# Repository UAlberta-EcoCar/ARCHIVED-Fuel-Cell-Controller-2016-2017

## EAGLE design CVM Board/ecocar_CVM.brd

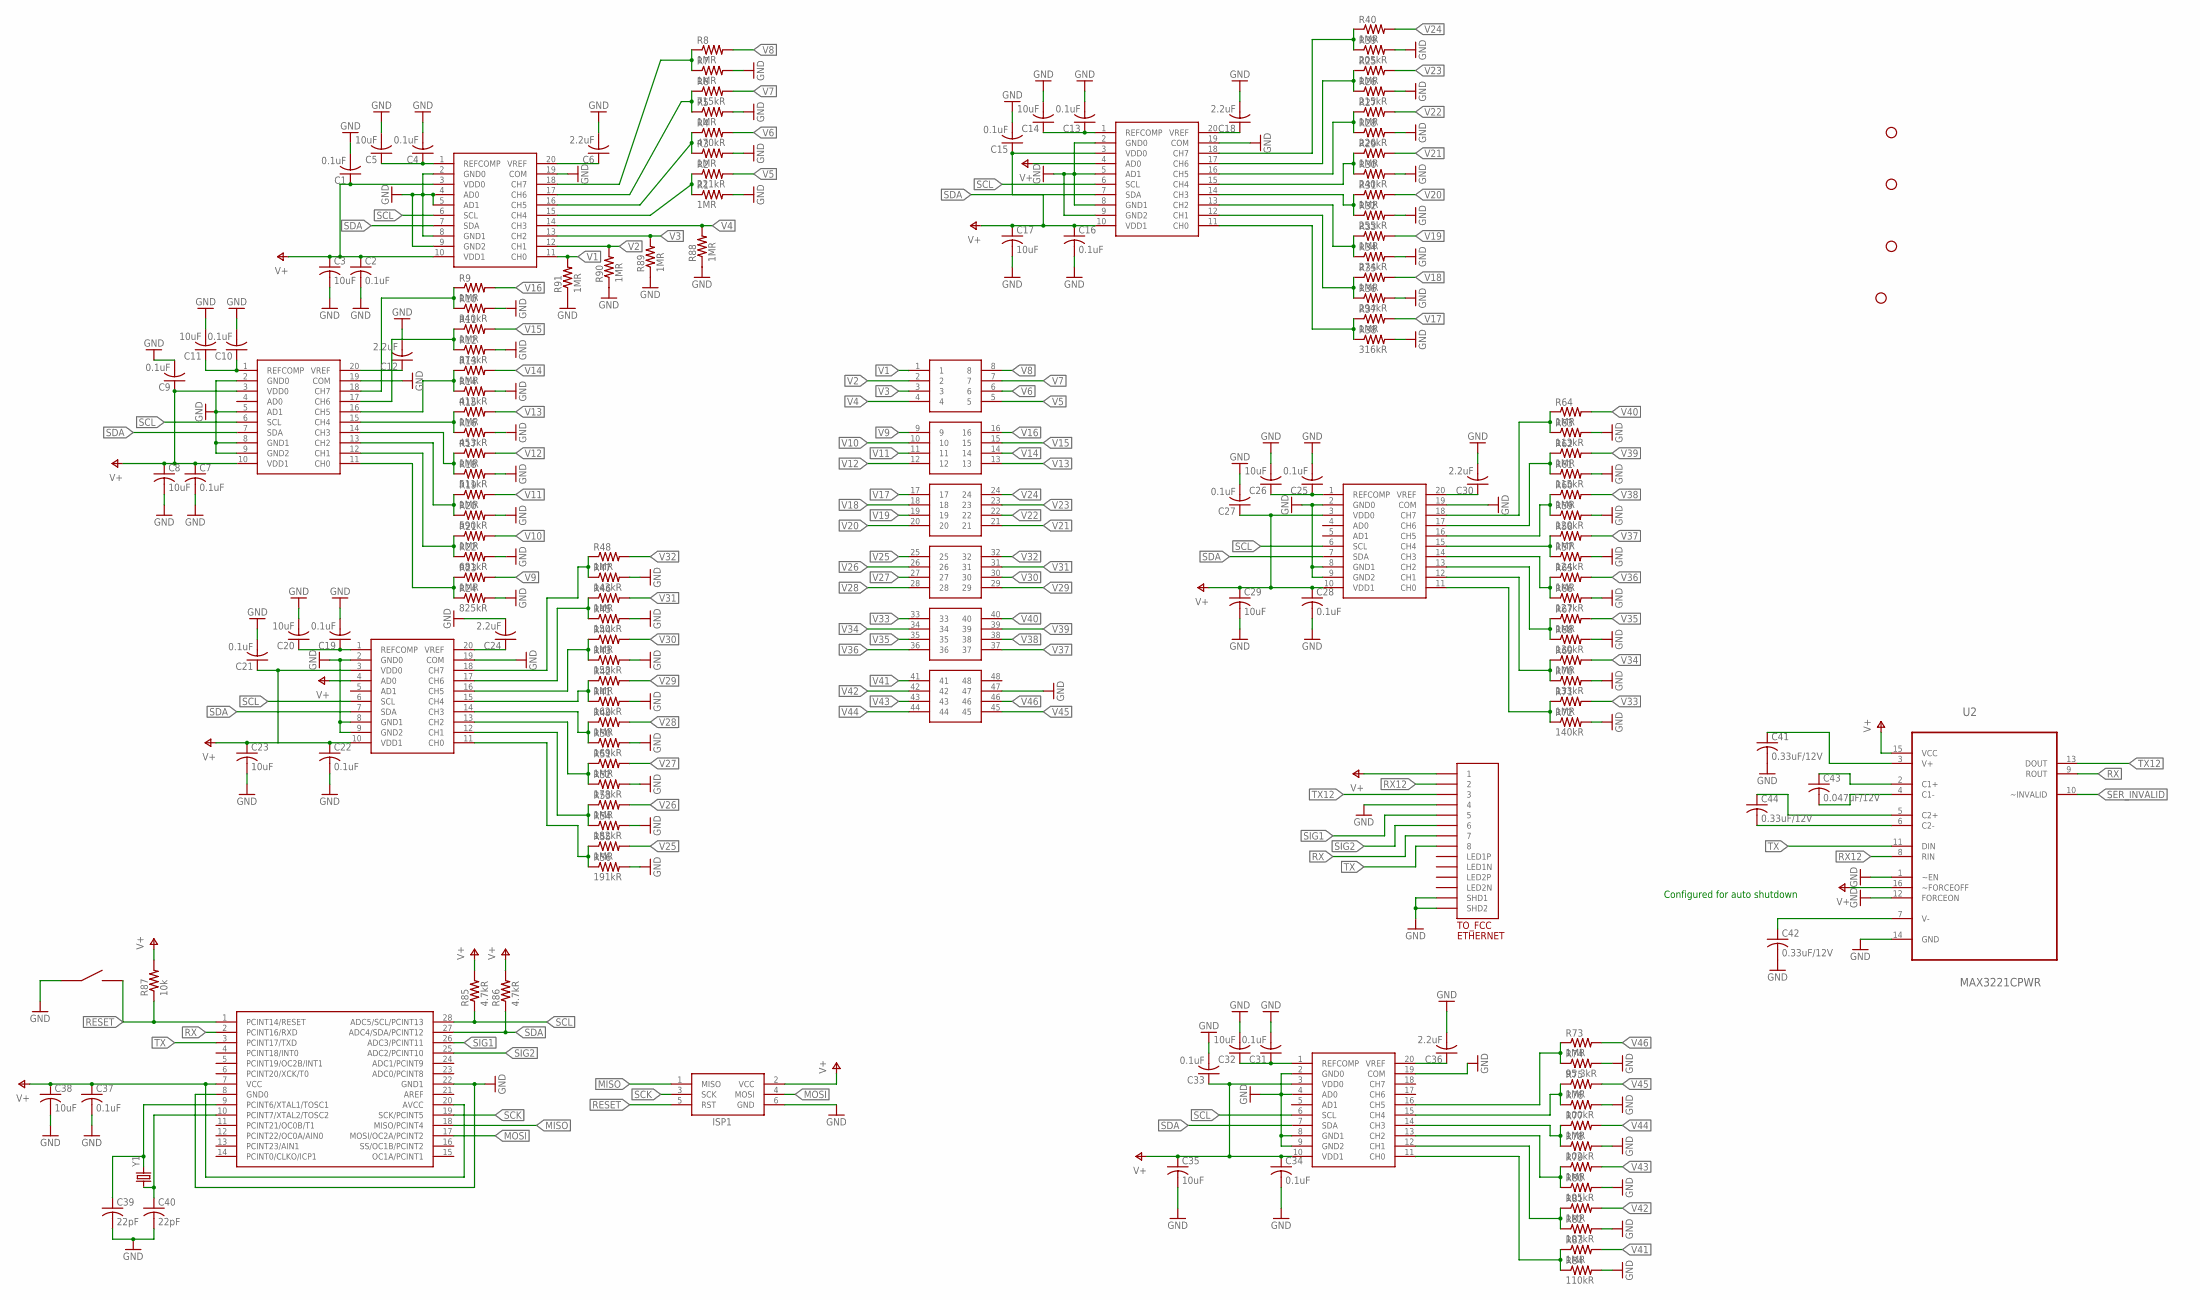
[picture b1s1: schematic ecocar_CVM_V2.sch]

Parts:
0001000, 0001001, 0001010, 0001011, 0011000, 0011001: LTC2309; TSSOP20
C1, C2, C4, C7, C9, C10, C13, C15, C16, C19, C21, C22, C25, C27, C28, C31, C33, C34, C37: 0.1uF; C0805
C3, C5, C8, C11, C14, C17, C20, C23, C26, C29, C32, C35, C38: 10uF; C0805
C6, C12, C18, C24, C30, C36: 2.2uF; C0805
C39, C40: 22pF; C0805
C41, C42, C44: 0.33uF/12V; C0805
C43: 0.047uF/12V; C0805
ISP1: AVRISP-BOX
R1, R3, R5, R7, R8, R9, R11, R13, R15, R17, R19, R21, R23, R25, R27, R29, R31, R33, R35, R37, R40, R42, R44, R46, R48, R49, R51, R53, R55, R58, R60, R62, R64, R65, R67, R69, R71, R73, R75, R77, R79, R81, R83, R88, R89, R90, R91: 1MR; R0805
R2: 221kR; R0805
R4: 470kR; R0805
R6: 715kR; R0805
R10: 340kR; R0805
R12: 374kR; R0805
R14: 412kR; R0805
R16: 453kR; R0805
R18: 511kR; R0805
R20: 590kR; R0805
R22: 681kR; R0805
R24: 825kR; R0805
R26: 215kR; R0805
R28: 226kR; R0805
R30: 240kR; R0805
R32: 255kR; R0805
R34: 274kR; R0805
R36: 294kR; R0805
R38: 316kR; R0805
R39: 205kR; R0805
R41: 162kR; R0805
R43: 158kR; R0805
R45: 150kR; R0805
R47: 143kR; R0805
R50: 169kR; R0805
R52: 178kR; R0805
R54: 182kR; R0805
R56: 191kR; R0805
R57: 124kR; R0805
R59: 120kR; R0805
R61: 115kR; R0805
R63: 113kR; R0805
R66: 127kR; R0805
R68: 130kR; R0805
R70: 133kR; R0805
R72: 140kR; R0805
R74: 95.3kR; R0805
R76: 100kR; R0805
R78: 102kR; R0805
R80: 105kR; R0805
R82: 107kR; R0805
R84: 110kR; R0805
R85, R86: 4.7kR; R0805
R87: 10k; R0805
RESET_BTN: EG4621CT-ND
STANDOFF1, STANDOFF2, STANDOFF3, STANDOFF4: STAND-OFF
TO_FCC: ETHERNET; A122645-ND
U2: MAX3221CPWR; SOP65P640X120-16N
U$1: ATMEGA328P; DIL28-3
U$3: 6-RJ45; 48-PIN-THROUGHHOLE
Y1: CRYSTALHC49US; HC49US

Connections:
GND: 0001000.2 (GND0), 0001000.4 (AD0), 0001000.5 (AD1), 0001000.8 (GND1), 0001000.9 (GND2), 0001000.19 (COM), 0001001.2 (GND0), 0001001.5 (AD1), 0001001.8 (GND1), 0001001.9 (GND2), 0001001.19 (COM), 0001010.2 (GND0), 0001010.5 (AD1), 0001010.8 (GND1), 0001010.9 (GND2), 0001010.19 (COM), 0001011.2 (GND0), 0001011.8 (GND1), 0001011.9 (GND2), 0001011.19 (COM), 0011000.2 (GND0), 0011000.8 (GND1), 0011000.9 (GND2), 0011000.19 (COM), 0011001.2 (GND0), 0011001.4 (AD0), 0011001.8 (GND1), 0011001.9 (GND2), 0011001.19 (COM), C1.2, C2.2, C3.2, C4.2, C5.2, C6.2, C7.2, C8.2, C9.2, C10.2, C11.2, C12.2, C13.2, C14.2, C15.2, C16.2, C17.2, C18.2, C19.2, C20.2, C21.2, C22.2, C23.2, C24.2, C25.2, C26.2, C27.2, C28.2, C29.2, C30.2, C31.2, C32.2, C33.2, C34.2, C35.2, C36.2, C37.2, C38.2, C39.2, C40.2, C41.2, C42.2, ISP1.6 (GND), R1.2, R3.2, R5.2, R7.2, R10.2, R12.2, R14.2, R16.2, R18.2, R20.2, R22.2, R24.2, R26.2, R28.2, R30.2, R32.2, R34.2, R36.2, R38.2, R39.2, R41.2, R43.2, R45.2, R47.2, R50.2, R52.2, R54.2, R56.2, R57.2, R59.2, R61.2, R63.2, R66.2, R68.2, R70.2, R72.2, R74.2, R76.2, R78.2, R80.2, R82.2, R84.2, R88.1, R89.1, R90.1, R91.1, RESET_BTN.P$1, TO_FCC.P$4 (4), TO_FCC.P$13 (SHD1), TO_FCC.P$14 (SHD2), U2.1 (~EN), U2.12 (FORCEON), U2.14 (GND), U$1.8 (GND0), U$1.22 (GND1), U$3.47; also elsewhere on the board
MISO: ISP1.1 (MISO), U$1.18 (MISO/PCINT4)
MOSI: ISP1.4 (MOSI), U$1.17 (MOSI/OC2A/PCINT2)
unnamed: 0001000.1 (REFCOMP), C4.1, C5.1
unnamed: 0001000.20 (VREF), C6.1
unnamed: 0001001.11 (CH0), R23.1, R24.1
unnamed: 0001001.1 (REFCOMP), C10.1, C11.1
unnamed: 0001001.20 (VREF), C12.1
unnamed: 0001001.12 (CH1), R21.1, R22.1
unnamed: 0001000.15 (CH4), R1.1, R2.1
unnamed: 0001000.16 (CH5), R3.1, R4.1
unnamed: 0001000.17 (CH6), R5.1, R6.1
unnamed: 0001000.18 (CH7), R7.1, R8.1
unnamed: 0001001.13 (CH2), R19.1, R20.1
unnamed: 0001001.14 (CH3), R17.1, R18.1
unnamed: 0001001.15 (CH4), R15.1, R16.1
unnamed: 0001001.16 (CH5), R13.1, R14.1
unnamed: 0001001.17 (CH6), R11.1, R12.1
unnamed: 0001001.18 (CH7), R9.1, R10.1
unnamed: 0001010.1 (REFCOMP), C13.1, C14.1
unnamed: 0011000.1 (REFCOMP), C25.1, C26.1
unnamed: 0001010.11 (CH0), R37.1, R38.1
unnamed: 0001010.20 (VREF), C18.1
unnamed: 0001010.12 (CH1), R35.1, R36.1
unnamed: 0001010.13 (CH2), R33.1, R34.1
unnamed: 0001010.14 (CH3), R31.1, R32.1
unnamed: 0001010.15 (CH4), R29.1, R30.1
unnamed: 0001010.16 (CH5), R27.1, R28.1
unnamed: 0001010.17 (CH6), R25.1, R26.1
unnamed: 0001010.18 (CH7), R39.1, R40.1
unnamed: 0001011.1 (REFCOMP), C19.1, C20.1
unnamed: 0011001.1 (REFCOMP), C31.1, C32.1
unnamed: 0011001.20 (VREF), C36.1
unnamed: 0001011.20 (VREF), C24.1
unnamed: 0001011.11 (CH0), R55.1, R56.1
unnamed: 0001011.12 (CH1), R53.1, R54.1
unnamed: 0001011.13 (CH2), R51.1, R52.1
unnamed: 0001011.14 (CH3), R49.1, R50.1
unnamed: 0001011.15 (CH4), R41.1, R42.1
unnamed: 0001011.16 (CH5), R43.1, R44.1
unnamed: 0001011.17 (CH6), R45.1, R46.1
unnamed: 0001011.18 (CH7), R47.1, R48.1
unnamed: 0011000.20 (VREF), C30.1
unnamed: 0011000.11 (CH0), R71.1, R72.1
unnamed: 0011000.12 (CH1), R69.1, R70.1
unnamed: 0011000.13 (CH2), R67.1, R68.1
unnamed: 0011000.14 (CH3), R65.1, R66.1
unnamed: 0011000.15 (CH4), R57.1, R58.1
unnamed: 0011000.16 (CH5), R59.1, R60.1
unnamed: 0011000.17 (CH6), R61.1, R62.1
unnamed: 0011000.18 (CH7), R63.1, R64.1
unnamed: C39.1, U$1.9 (PCINT6/XTAL1/TOSC1), Y1.2
unnamed: C40.1, U$1.10 (PCINT7/XTAL2/TOSC2), Y1.1
unnamed: 0011001.11 (CH0), R83.1, R84.1
unnamed: 0011001.12 (CH1), R81.1, R82.1
unnamed: 0011001.13 (CH2), R79.1, R80.1
unnamed: 0011001.14 (CH3), R77.1, R78.1
unnamed: 0011001.15 (CH4), R75.1, R76.1
unnamed: 0011001.16 (CH5), R73.1, R74.1
unnamed: C41.1, U2.3 (V+)
unnamed: C43.1, U2.2 (C1+)
unnamed: C43.2, U2.4 (C1-)
unnamed: C44.1, U2.5 (C2+)
unnamed: C44.2, U2.6 (C2-)
unnamed: C42.1, U2.7 (V-)
RESET: ISP1.5 (RST), R87.1, RESET_BTN.P$3, U$1.1 (PCINT14/RESET); also elsewhere on the board
RX12: TO_FCC.P$2 (2), U2.8 (RIN)
SCK: ISP1.3 (SCK), U$1.19 (SCK/PCINT5)
SCL: 0001000.6 (SCL), 0001001.6 (SCL), 0001010.6 (SCL), 0001011.6 (SCL), 0011000.6 (SCL), 0011001.6 (SCL), R85.1, U$1.28 (ADC5/SCL/PCINT13)
SDA: 0001000.7 (SDA), 0001001.7 (SDA), 0001010.7 (SDA), 0001011.7 (SDA), 0011000.7 (SDA), 0011001.7 (SDA), R86.1, U$1.27 (ADC4/SDA/PCINT12)
SER_INVALID: U2.10 (~INVALID)
SIG1: TO_FCC.P$5 (5), U$1.26 (ADC3/PCINT11)
SIG2: TO_FCC.P$6 (6), U$1.25 (ADC2/PCINT10)
TX12: TO_FCC.P$3 (3), U2.13 (DOUT)
V1: 0001000.11 (CH0), R91.2, U$3.1
V2: 0001000.12 (CH1), R90.2, U$3.2
V3: 0001000.13 (CH2), R89.2, U$3.3
V4: 0001000.14 (CH3), R88.2, U$3.4
V5: R2.2, U$3.5
V6: R4.2, U$3.6
V7: R6.2, U$3.7
V8: R8.2, U$3.8
V9: R23.2, U$3.9
V10: R21.2, U$3.10
V11: R19.2, U$3.11
V12: R17.2, U$3.12
V13: R15.2, U$3.13
V14: R13.2, U$3.14
V15: R11.2, U$3.15
V16: R9.2, U$3.16
V17: R37.2, U$3.17
V18: R35.2, U$3.18
V19: R33.2, U$3.19
V20: R31.2, U$3.20
V21: R29.2, U$3.21
V22: R27.2, U$3.22
V23: R25.2, U$3.23
V24: R40.2, U$3.24
V25: R55.2, U$3.25
V26: R53.2, U$3.26
V27: R51.2, U$3.27
V28: R49.2, U$3.28
V29: R42.2, U$3.29
V30: R44.2, U$3.30
V31: R46.2, U$3.31
V32: R48.2, U$3.32
V33: R71.2, U$3.33
V34: R69.2, U$3.34
V35: R67.2, U$3.35
V36: R65.2, U$3.36
V37: R58.2, U$3.37
V38: R60.2, U$3.38
V39: R62.2, U$3.39
V40: R64.2, U$3.40
V41: R83.2, U$3.41
V42: R81.2, U$3.42
V43: R79.2, U$3.43
V44: R77.2, U$3.44
V45: R75.2, U$3.45
V46: R73.2, U$3.46
V+: 0001000.3 (VDD0), 0001000.10 (VDD1), 0001001.3 (VDD0), 0001001.10 (VDD1), 0001010.3 (VDD0), 0001010.4 (AD0), 0001010.10 (VDD1), 0001011.3 (VDD0), 0001011.4 (AD0), 0001011.10 (VDD1), 0011000.3 (VDD0), 0011000.10 (VDD1), 0011001.3 (VDD0), 0011001.10 (VDD1), C1.1, C2.1, C3.1, C7.1, C8.1, C9.1, C15.1, C16.1, C17.1, C21.1, C22.1, C23.1, C27.1, C28.1, C29.1, C33.1, C34.1, C35.1, C37.1, C38.1, ISP1.2 (VCC), R85.2, R86.2, R87.2, TO_FCC.P$1 (1), U2.15 (VCC), U2.16 (~FORCEOFF), U$1.7 (VCC), U$1.20 (AVCC)

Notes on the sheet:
Configured for auto shutdown

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
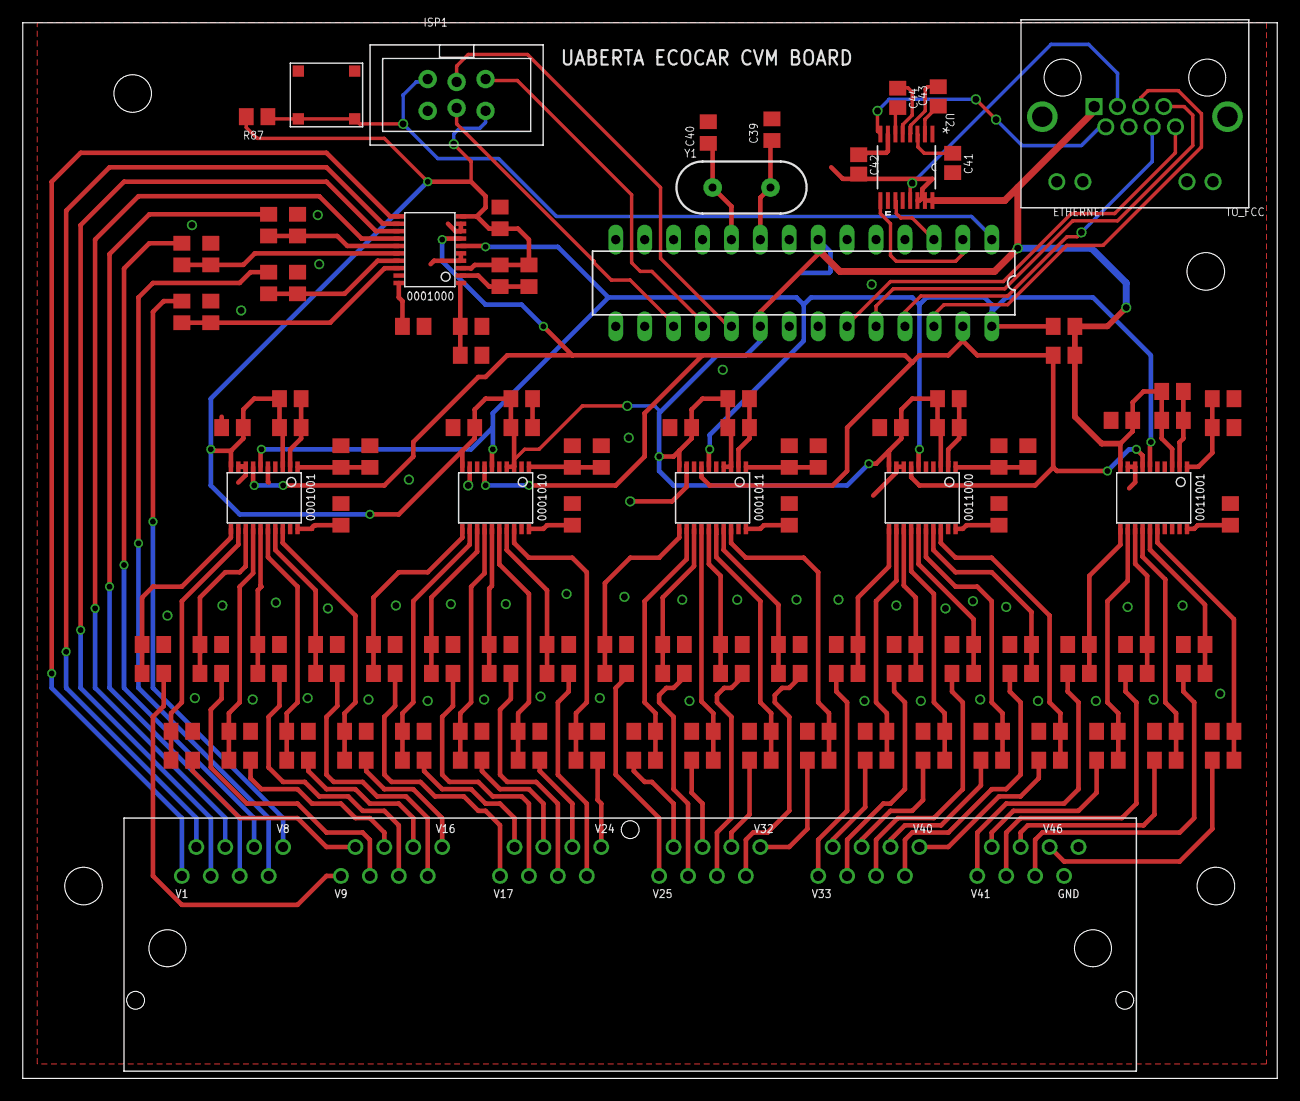
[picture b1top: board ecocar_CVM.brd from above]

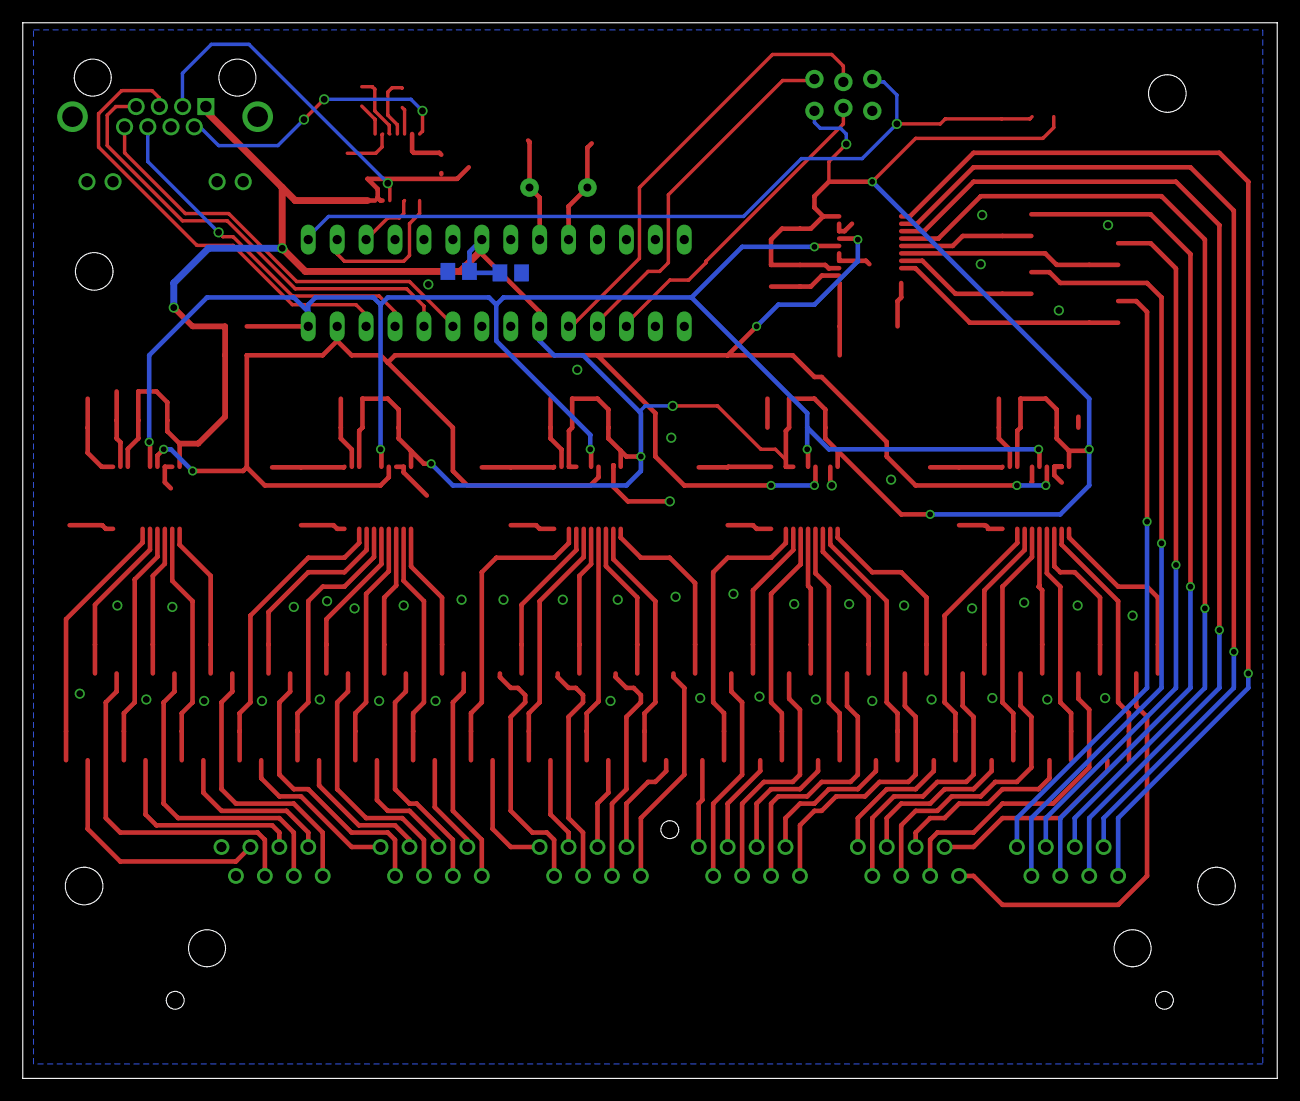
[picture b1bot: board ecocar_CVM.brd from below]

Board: 2 copper layers, 110.2 x 92.7 mm, 148 parts (2 on the bottom side), 124 nets.

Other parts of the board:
U$4: EG4621CT-ND

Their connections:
GND: U$4.P$1, U$4.P$2; also elsewhere on the board
RESET: U$4.P$3, U$4.P$4; also elsewhere on the board

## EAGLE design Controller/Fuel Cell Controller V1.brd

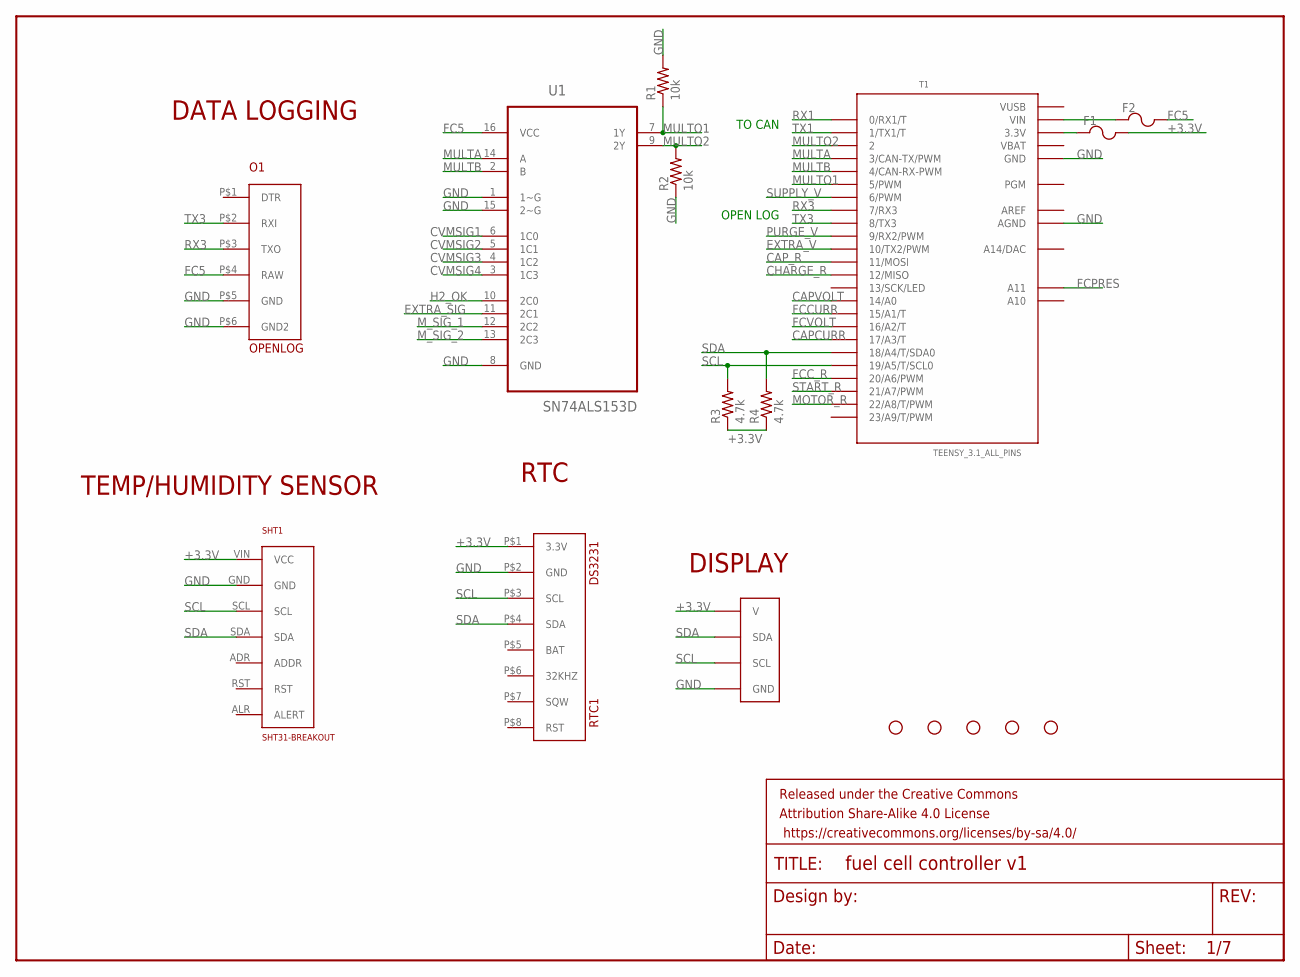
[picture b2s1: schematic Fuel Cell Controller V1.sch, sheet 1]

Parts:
F1, F2: POLYFUSE; 1206
FRAME1: FRAME-LETTERNO_PACKAGE; DUMMY
LCD1: LCD-BOARD
O1: OPENLOG
R1, R2: 10k; 0805
R3, R4: 4.7k; 0805
RTC1: DS3231
SHT1: SHT31-BREAKOUT
STANDOFF1, STANDOFF2, STANDOFF3, STANDOFF4, STANDOFF5: STAND-OFF
T1: TEENSY_3.1_ALL_PINS; TEENSY3-ALL_PINS
U1: SN74ALS153D; SOIC127P600X175-16N

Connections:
+3.3V: F1.2, LCD1.V, R3.1, R4.1, RTC1.P$1 (3.3V), SHT1.VIN (VCC); also elsewhere on the board
AREF: T1.AREF
CAPCURR: T1.17/A3 (17/A3/T); also elsewhere on the board
CAPVOLT: T1.14/A0; also elsewhere on the board
CAP_R: T1.11 (11/MOSI); also elsewhere on the board
CHARGE_R: T1.12 (12/MISO); also elsewhere on the board
CVMSIG1: U1.6 (1C0); also elsewhere on the board
CVMSIG2: U1.5 (1C1); also elsewhere on the board
CVMSIG3: U1.4 (1C2); also elsewhere on the board
CVMSIG4: U1.3 (1C3); also elsewhere on the board
EXTRA_SIG: U1.11 (2C1); also elsewhere on the board
EXTRA_V: T1.10 (10/TX2/PWM); also elsewhere on the board
FC5: F2.2, O1.P$4 (RAW), U1.16 (VCC); also elsewhere on the board
FCCURR: T1.15/A1 (15/A1/T); also elsewhere on the board
FCC_R: T1.20/A6 (20/A6/PWM); also elsewhere on the board
FCPRES: T1.A11; also elsewhere on the board
FCVOLT: T1.16/A2 (16/A2/T); also elsewhere on the board
GND: LCD1.GND1 (GND), LCD1.GND2 (GND), LCD1.GND3 (GND), LCD1.GND4 (GND), LCD1.GND5 (GND), LCD1.GND6 (GND), LCD1.GND7 (GND), LCD1.GND8 (GND), LCD1.GND9 (GND), LCD1.GND10 (GND), LCD1.GND11 (GND), LCD1.GND12 (GND), LCD1.GND13 (GND), O1.P$5 (GND), O1.P$6 (GND2), R1.2, R2.1, RTC1.P$2 (GND), SHT1.GND, T1.AGND, T1.GND, T1.GND1 (GND), U1.1 (1~G), U1.8 (GND), U1.15 (2~G); also elsewhere on the board
H2_OK: U1.10 (2C0); also elsewhere on the board
MOTOR_R: T1.22/A8 (22/A8/T/PWM); also elsewhere on the board
MULTA: T1.3 (3/CAN-TX/PWM), U1.14 (A)
MULTB: T1.4 (4/CAN-RX-PWM), U1.2 (B)
MULTO1: R1.1, T1.5 (5/PWM), U1.7 (1Y)
MULTO2: R2.2, T1.2, U1.9 (2Y)
M_SIG_1: U1.12 (2C2); also elsewhere on the board
M_SIG_2: U1.13 (2C3); also elsewhere on the board
unnamed: F2.1, T1.VIN
unnamed: F1.1, T1.3.3V, T1.3.3V1 (3.3V)
PURGE_V: T1.9 (9/RX2/PWM); also elsewhere on the board
RX1: T1.0 (0/RX1/T); also elsewhere on the board
RX3: O1.P$3 (TXO), T1.7 (7/RX3)
SCL: LCD1.SCL, R3.2, RTC1.P$3 (SCL), SHT1.SCL, T1.19/A5 (19/A5/T/SCL0); also elsewhere on the board
SDA: LCD1.SDA, R4.2, RTC1.P$4 (SDA), SHT1.SDA, T1.18/A4 (18/A4/T/SDA0); also elsewhere on the board
START_R: T1.21/A7 (21/A7/PWM); also elsewhere on the board
SUPPLY_V: T1.6 (6/PWM); also elsewhere on the board
TX1: T1.1 (1/TX1/T); also elsewhere on the board
TX3: O1.P$2 (RXI), T1.8 (8/TX3)
VBAT: T1.VBAT
VUSB: T1.VUSB

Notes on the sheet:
TO CAN
OPEN LOG
DISPLAY
DATA LOGGING
TEMP/HUMIDITY SENSOR
RTC

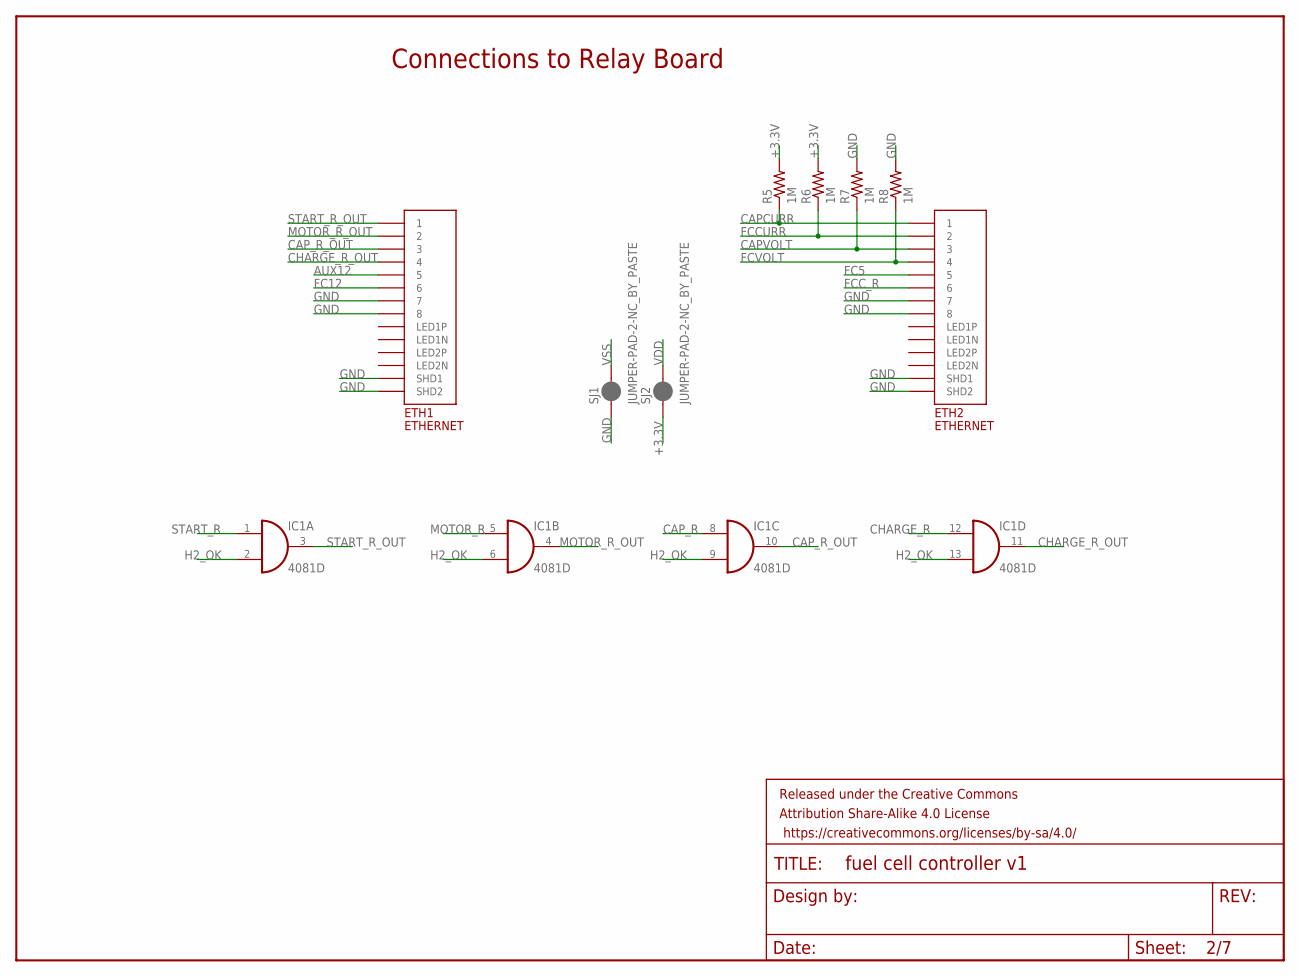
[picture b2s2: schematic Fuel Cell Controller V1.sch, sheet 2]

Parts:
ETH1, ETH2: ETHERNET; A122645-ND
FRAME2: FRAME-LETTERNO_PACKAGE; DUMMY
IC1: 4081D; SO14
R5, R6, R7, R8: 1M; 0805
SJ1, SJ2: JUMPER-PAD-2-NC_BY_PASTE; PAD-JUMPER-2-NC_BY_PASTE_YES_SILK

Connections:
+3.3V: R5.2, R6.2, SJ2.1; also elsewhere on the board
AUX12: ETH1.P$5 (5); also elsewhere on the board
CAPCURR: ETH2.P$1 (1), R5.1; also elsewhere on the board
CAPVOLT: ETH2.P$3 (3), R7.1; also elsewhere on the board
CAP_R: IC1.8 (I0); also elsewhere on the board
CAP_R_OUT: ETH1.P$3 (3), IC1.10 (O)
CHARGE_R: IC1.12 (I0); also elsewhere on the board
CHARGE_R_OUT: ETH1.P$4 (4), IC1.11 (O)
FC5: ETH2.P$5 (5); also elsewhere on the board
FC12: ETH1.P$6 (6); also elsewhere on the board
FCCURR: ETH2.P$2 (2), R6.1; also elsewhere on the board
FCC_R: ETH2.P$6 (6); also elsewhere on the board
FCVOLT: ETH2.P$4 (4), R8.1; also elsewhere on the board
GND: ETH1.P$7 (7), ETH1.P$8 (8), ETH1.P$13 (SHD1), ETH1.P$14 (SHD2), ETH2.P$7 (7), ETH2.P$8 (8), ETH2.P$13 (SHD1), ETH2.P$14 (SHD2), R7.2, R8.2, SJ1.1; also elsewhere on the board
H2_OK: IC1.2 (I1), IC1.6 (I1), IC1.9 (I1), IC1.13 (I1); also elsewhere on the board
MOTOR_R: IC1.5 (I0); also elsewhere on the board
MOTOR_R_OUT: ETH1.P$2 (2), IC1.4 (O)
START_R: IC1.1 (I0); also elsewhere on the board
START_R_OUT: ETH1.P$1 (1), IC1.3 (O)
VDD: IC1.14 (VDD), SJ2.2
VSS: IC1.7 (VSS), SJ1.2

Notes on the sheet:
Connections to Relay Board

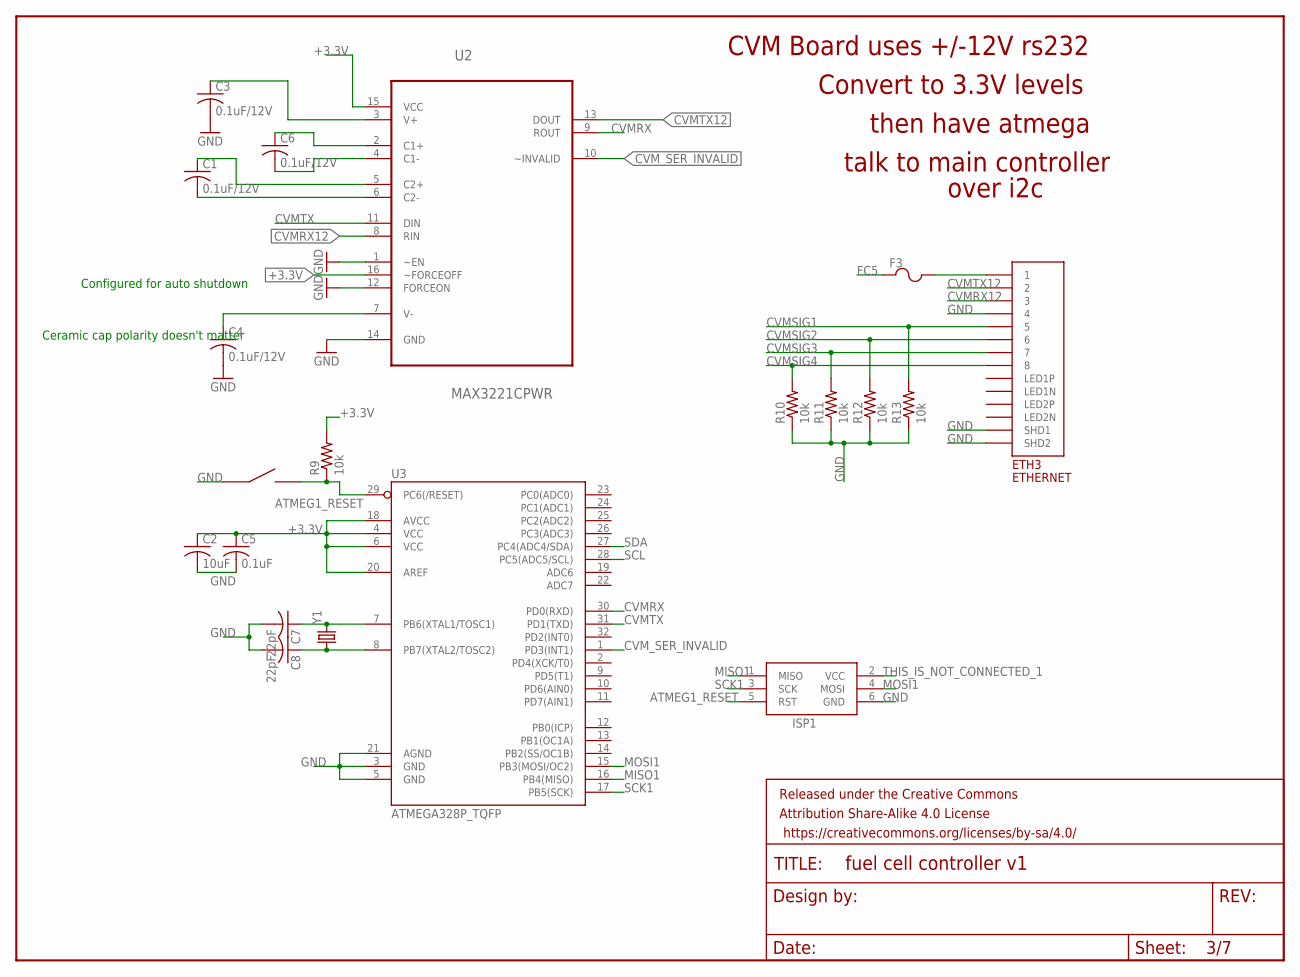
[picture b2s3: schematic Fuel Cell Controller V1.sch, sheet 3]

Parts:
C1, C3, C4, C6: 0.1uF/12V; C0805
C2: 10uF; C0603
C5: 0.1uF; C0603
C7, C8: 22pF; C0603
ETH3: ETHERNET; A122645-ND
F3: POLYFUSE; 1206
FRAME3: FRAME-LETTERNO_PACKAGE; DUMMY
ISP1: AVRISP-BOX
R9: 10k; R0603
R10, R11, R12, R13: 10k; 0805
S1: EG4621CT-ND
U2: MAX3221CPWR; SOP65P640X120-16N
U3: ATMEGA328P_TQFP; TQFP32-08
Y1: CRYSTALHC49US; HC49US

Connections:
+3.3V: C2.1, C5.1, R9.2, U2.15 (VCC), U2.16 (~FORCEOFF), U3.4 (VCC), U3.6 (VCC), U3.18 (AVCC), U3.20 (AREF); also elsewhere on the board
ATMEG1_RESET: ISP1.5 (RST), R9.1, S1.P$3, S1.P$4, U3.29 (PC6(/RESET))
CVMRX: U2.9 (ROUT), U3.30 (PD0(RXD))
CVMRX12: ETH3.P$3 (3), U2.8 (RIN)
CVMSIG1: ETH3.P$5 (5), R13.2; also elsewhere on the board
CVMSIG2: ETH3.P$6 (6), R12.2; also elsewhere on the board
CVMSIG3: ETH3.P$7 (7), R11.2; also elsewhere on the board
CVMSIG4: ETH3.P$8 (8), R10.2; also elsewhere on the board
CVMTX: U2.11 (DIN), U3.31 (PD1(TXD))
CVMTX12: ETH3.P$2 (2), U2.13 (DOUT)
CVM_SER_INVALID: U2.10 (~INVALID), U3.1 (PD3(INT1))
FC5: F3.1; also elsewhere on the board
GND: C2.2, C3.2, C4.2, C5.2, C7.2, C8.2, ETH3.P$4 (4), ETH3.P$13 (SHD1), ETH3.P$14 (SHD2), ISP1.6 (GND), R10.1, R11.1, R12.1, R13.1, S1.P$1, S1.P$2, U2.1 (~EN), U2.12 (FORCEON), U2.14 (GND), U3.3 (GND), U3.5 (GND), U3.21 (AGND); also elsewhere on the board
MISO1: ISP1.1 (MISO), U3.16 (PB4(MISO))
MOSI1: ISP1.4 (MOSI), U3.15 (PB3(MOSI/OC2))
unnamed: C7.1, U3.7 (PB6(XTAL1/TOSC1)), Y1.2
unnamed: C8.1, U3.8 (PB7(XTAL2/TOSC2)), Y1.1
unnamed: ETH3.P$1 (1), F3.2
unnamed: C3.1, U2.3 (V+)
unnamed: C6.1, U2.2 (C1+)
unnamed: C6.2, U2.4 (C1-)
unnamed: C1.1, U2.5 (C2+)
unnamed: C1.2, U2.6 (C2-)
unnamed: C4.1, U2.7 (V-)
SCK1: ISP1.3 (SCK), U3.17 (PB5(SCK))
SCL: U3.28 (PC5(ADC5/SCL)); also elsewhere on the board
SDA: U3.27 (PC4(ADC4/SDA)); also elsewhere on the board
THIS_IS_NOT_CONNECTED_1: ISP1.2 (VCC)

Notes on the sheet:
Configured for auto shutdown
CVM Board uses +/-12V rs232
Convert to 3.3V levels
then have atmega
talk to main controller
over i2c
Ceramic cap polarity doesn't matter

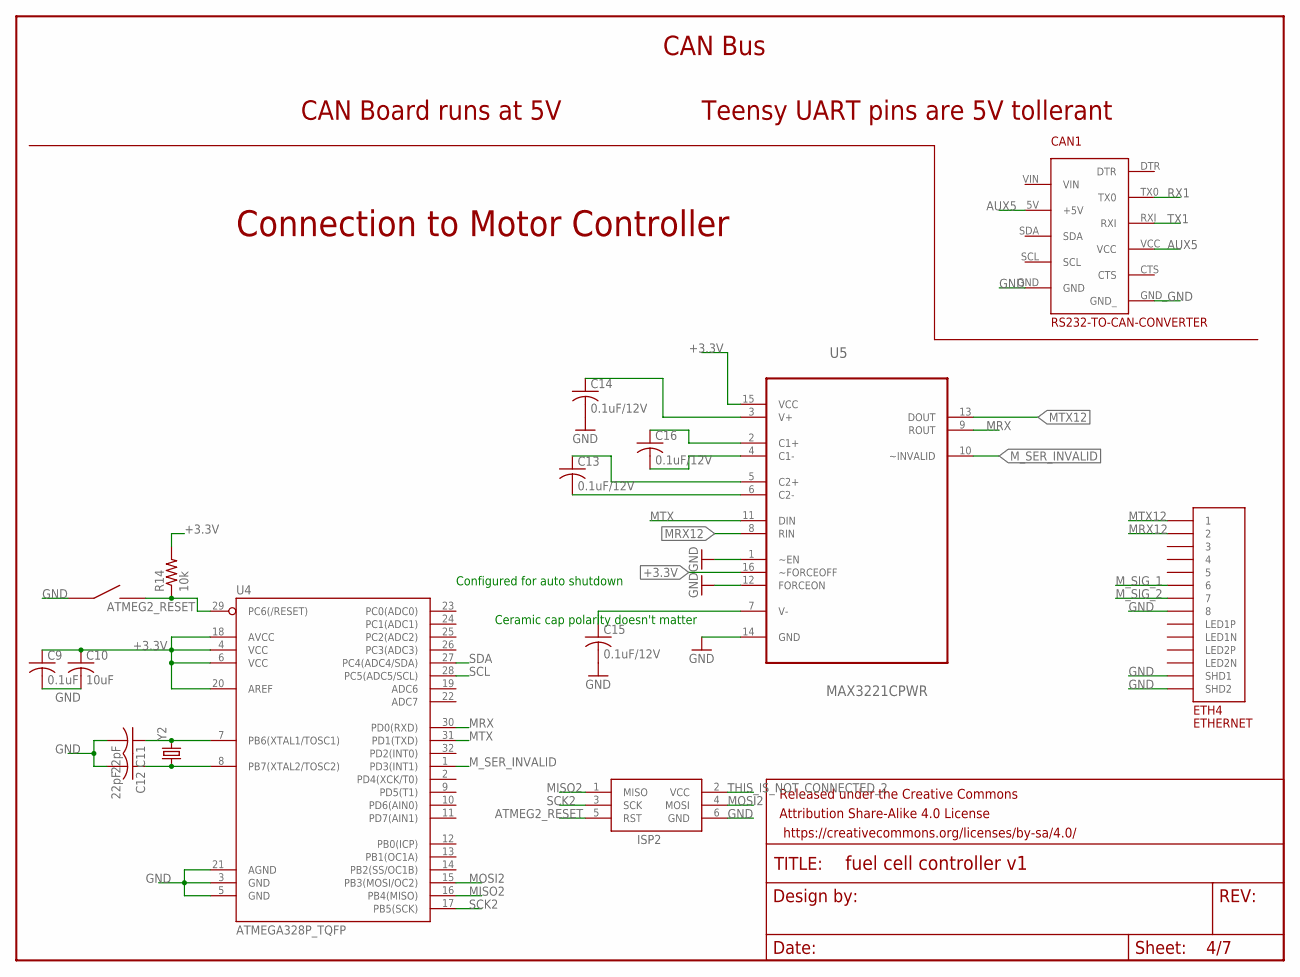
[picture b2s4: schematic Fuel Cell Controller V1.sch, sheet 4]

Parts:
C9: 0.1uF; C0603
C10: 10uF; C0603
C11, C12: 22pF; C0603
C13, C14, C15, C16: 0.1uF/12V; C0805
CAN1: RS232-TO-CAN-CONVERTER
ETH4: ETHERNET; A122645-ND
FRAME4: FRAME-LETTERNO_PACKAGE; DUMMY
ISP2: AVRISP-BOX
R14: 10k; R0603
S2: EG4621CT-ND
U4: ATMEGA328P_TQFP; TQFP32-08
U5: MAX3221CPWR; SOP65P640X120-16N
Y2: CRYSTALHC49US; HC49US

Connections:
+3.3V: C9.1, C10.1, R14.2, U4.4 (VCC), U4.6 (VCC), U4.18 (AVCC), U4.20 (AREF), U5.15 (VCC), U5.16 (~FORCEOFF); also elsewhere on the board
ATMEG2_RESET: ISP2.5 (RST), R14.1, S2.P$3, S2.P$4, U4.29 (PC6(/RESET))
AUX5: CAN1.5V (+5V), CAN1.VCC; also elsewhere on the board
GND: C9.2, C10.2, C11.2, C12.2, C14.2, C15.2, CAN1.GND, CAN1.GND_, ETH4.P$8 (8), ETH4.P$13 (SHD1), ETH4.P$14 (SHD2), ISP2.6 (GND), S2.P$1, S2.P$2, U4.3 (GND), U4.5 (GND), U4.21 (AGND), U5.1 (~EN), U5.12 (FORCEON), U5.14 (GND); also elsewhere on the board
MISO2: ISP2.1 (MISO), U4.16 (PB4(MISO))
MOSI2: ISP2.4 (MOSI), U4.15 (PB3(MOSI/OC2))
MRX: U4.30 (PD0(RXD)), U5.9 (ROUT)
MRX12: ETH4.P$2 (2), U5.8 (RIN)
MTX: U4.31 (PD1(TXD)), U5.11 (DIN)
MTX12: ETH4.P$1 (1), U5.13 (DOUT)
M_SER_INVALID: U4.1 (PD3(INT1)), U5.10 (~INVALID)
M_SIG_1: ETH4.P$6 (6); also elsewhere on the board
M_SIG_2: ETH4.P$7 (7); also elsewhere on the board
unnamed: C11.1, U4.7 (PB6(XTAL1/TOSC1)), Y2.2
unnamed: C12.1, U4.8 (PB7(XTAL2/TOSC2)), Y2.1
unnamed: C14.1, U5.3 (V+)
unnamed: C16.1, U5.2 (C1+)
unnamed: C16.2, U5.4 (C1-)
unnamed: C13.1, U5.5 (C2+)
unnamed: C13.2, U5.6 (C2-)
unnamed: C15.1, U5.7 (V-)
RX1: CAN1.TX0; also elsewhere on the board
SCK2: ISP2.3 (SCK), U4.17 (PB5(SCK))
SCL: U4.28 (PC5(ADC5/SCL)); also elsewhere on the board
SDA: U4.27 (PC4(ADC4/SDA)); also elsewhere on the board
THIS_IS_NOT_CONNECTED_2: ISP2.2 (VCC)
TX1: CAN1.RXI; also elsewhere on the board

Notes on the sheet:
CAN Bus
CAN Board runs at 5V
Teensy UART pins are 5V tollerant
Connection to Motor Controller
Configured for auto shutdown
Ceramic cap polarity doesn't matter

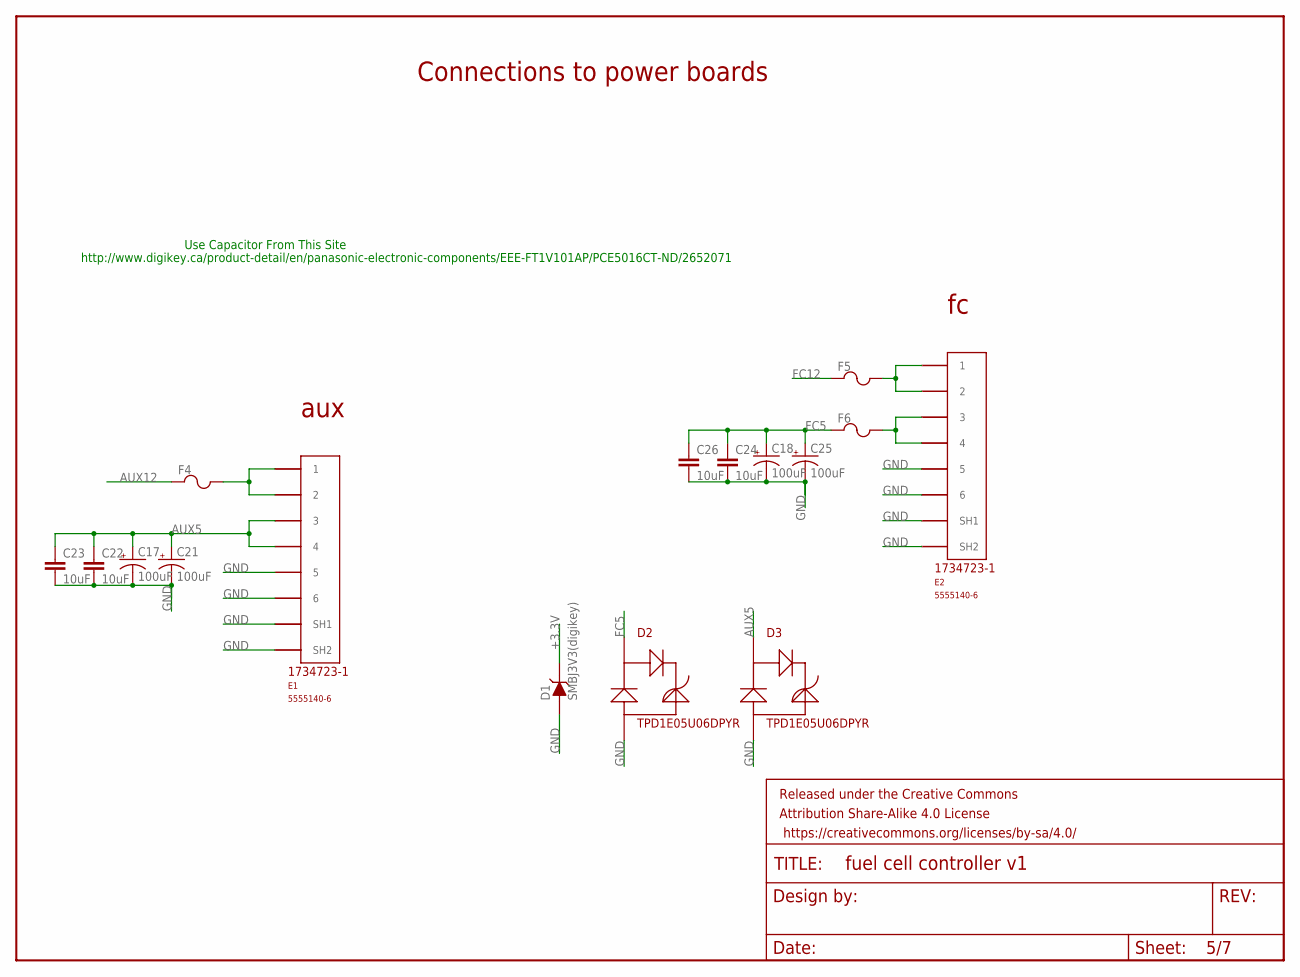
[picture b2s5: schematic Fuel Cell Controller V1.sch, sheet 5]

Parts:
C17, C18, C21, C25: 100uF; PANASONIC_D
C22, C23, C24, C26: 10uF; 0805
D1: SMBJ3V3(digikey); DO-214AB
D2, D3: TPD1E05U06DPYR; 2-XDFN
E1, E2: 5555140-6; 1734723-1_RJ11
F4, F5, F6: POLYFUSE; 1206
FRAME5: FRAME-LETTERNO_PACKAGE; DUMMY

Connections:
+3.3V: D1.C; also elsewhere on the board
AUX5: C17.+, C21.+, C22.1, C23.1, D3.P$1, E1.3, E1.4; also elsewhere on the board
AUX12: F4.1; also elsewhere on the board
FC5: C18.+, C24.1, C25.+, C26.1, D2.P$1, F6.1; also elsewhere on the board
FC12: F5.1; also elsewhere on the board
GND: C17.-, C18.-, C21.-, C22.2, C23.2, C24.2, C25.-, C26.2, D1.A, D2.P$2, D3.P$2, E1.5, E1.6, E1.SH1, E1.SH2, E2.5, E2.6, E2.SH1, E2.SH2; also elsewhere on the board
unnamed: E1.1, E1.2, F4.2
unnamed: E2.1, E2.2, F5.2
unnamed: E2.3, E2.4, F6.2

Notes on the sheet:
Connections to power boards
aux
Use Capacitor From This Site
http://www.digikey.ca/product-detail/en/panasonic-electronic-components/EEE-FT1V101AP/PCE5016CT-ND/2652071

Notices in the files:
parts and their libraries:
SparkFun-FreqCtrl: Licensing: Creative Commons ShareAlike 4.0 International - https://creativecommons.org/licenses/by-sa/4.0
SparkFun-Aesthetics: Released under the Creative Commons Attribution Share-Alike 4.0 License
SparkFun-Aesthetics: https://creativecommons.org/licenses/by-sa/4.0
